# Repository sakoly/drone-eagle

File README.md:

# drone-eaglefile
ドローン制御用基板データ
dronesel5は電源用（フライトコントローラーとescに給電）
drone5はフライトコントローラー

基板作成支援アプリeagleで作成したドローンの基板データ
dps310(気圧センサ)：spi接続
minigps(みちびき対応GPS):uart接続
mpu9250(9軸センサ):spi接続
twelite(通信機):uart接続
HC-SR04(超音波センサ):degitalread(HIorLO)

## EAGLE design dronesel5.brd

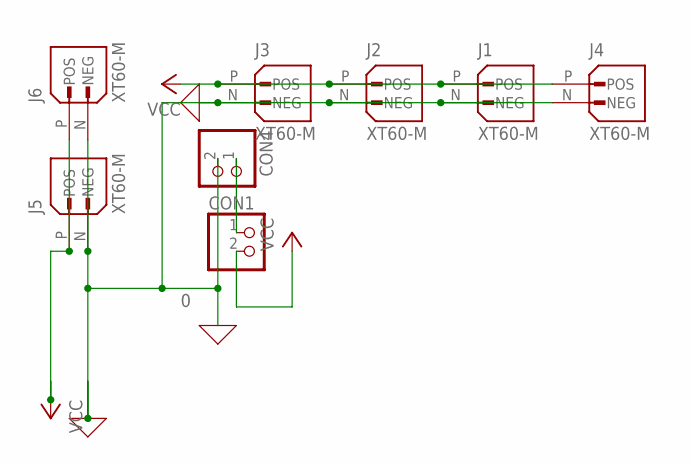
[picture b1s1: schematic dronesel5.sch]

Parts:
CON1, CON4: L2; L_2
J1, J2, J3, J4, J5, J6: XT60-M; AMASS_XT60-M

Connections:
0: CON4.2, J1.N (NEG), J2.N (NEG), J3.N (NEG), J4.N (NEG), J5.N (NEG), J6.N (NEG)
unnamed: CON1.1 (GND), CON4.1 (GND)
VCC: CON1.2, J1.P (POS), J2.P (POS), J3.P (POS), J4.P (POS), J5.P (POS), J6.P (POS)

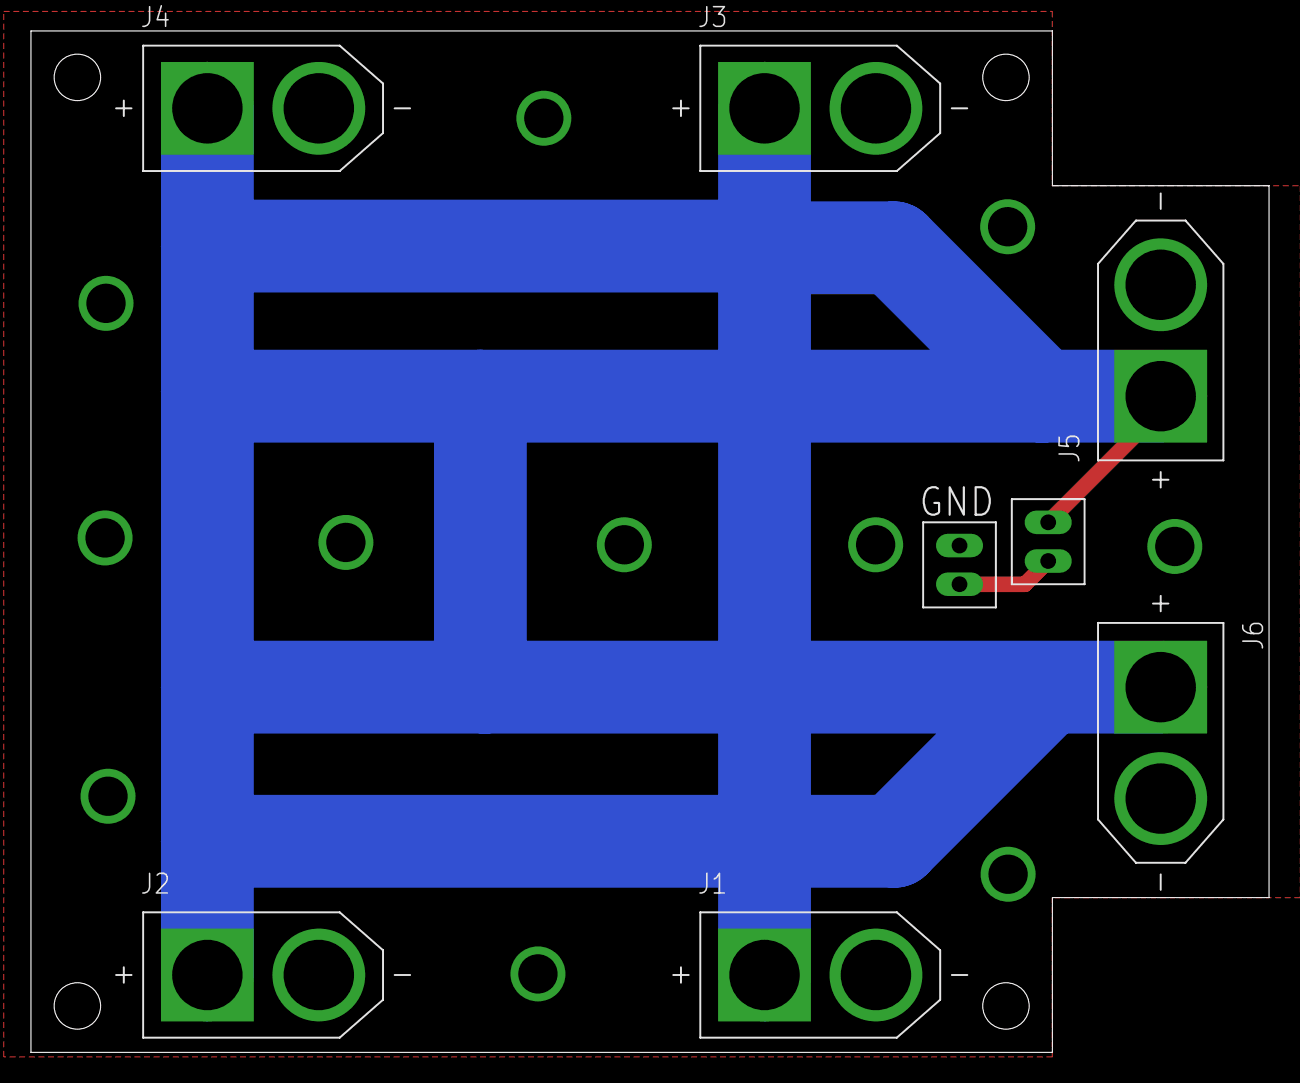
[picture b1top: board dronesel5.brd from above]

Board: 2 copper layers, 80.0 x 66.0 mm, 8 parts (0 on the bottom side), 3 nets.

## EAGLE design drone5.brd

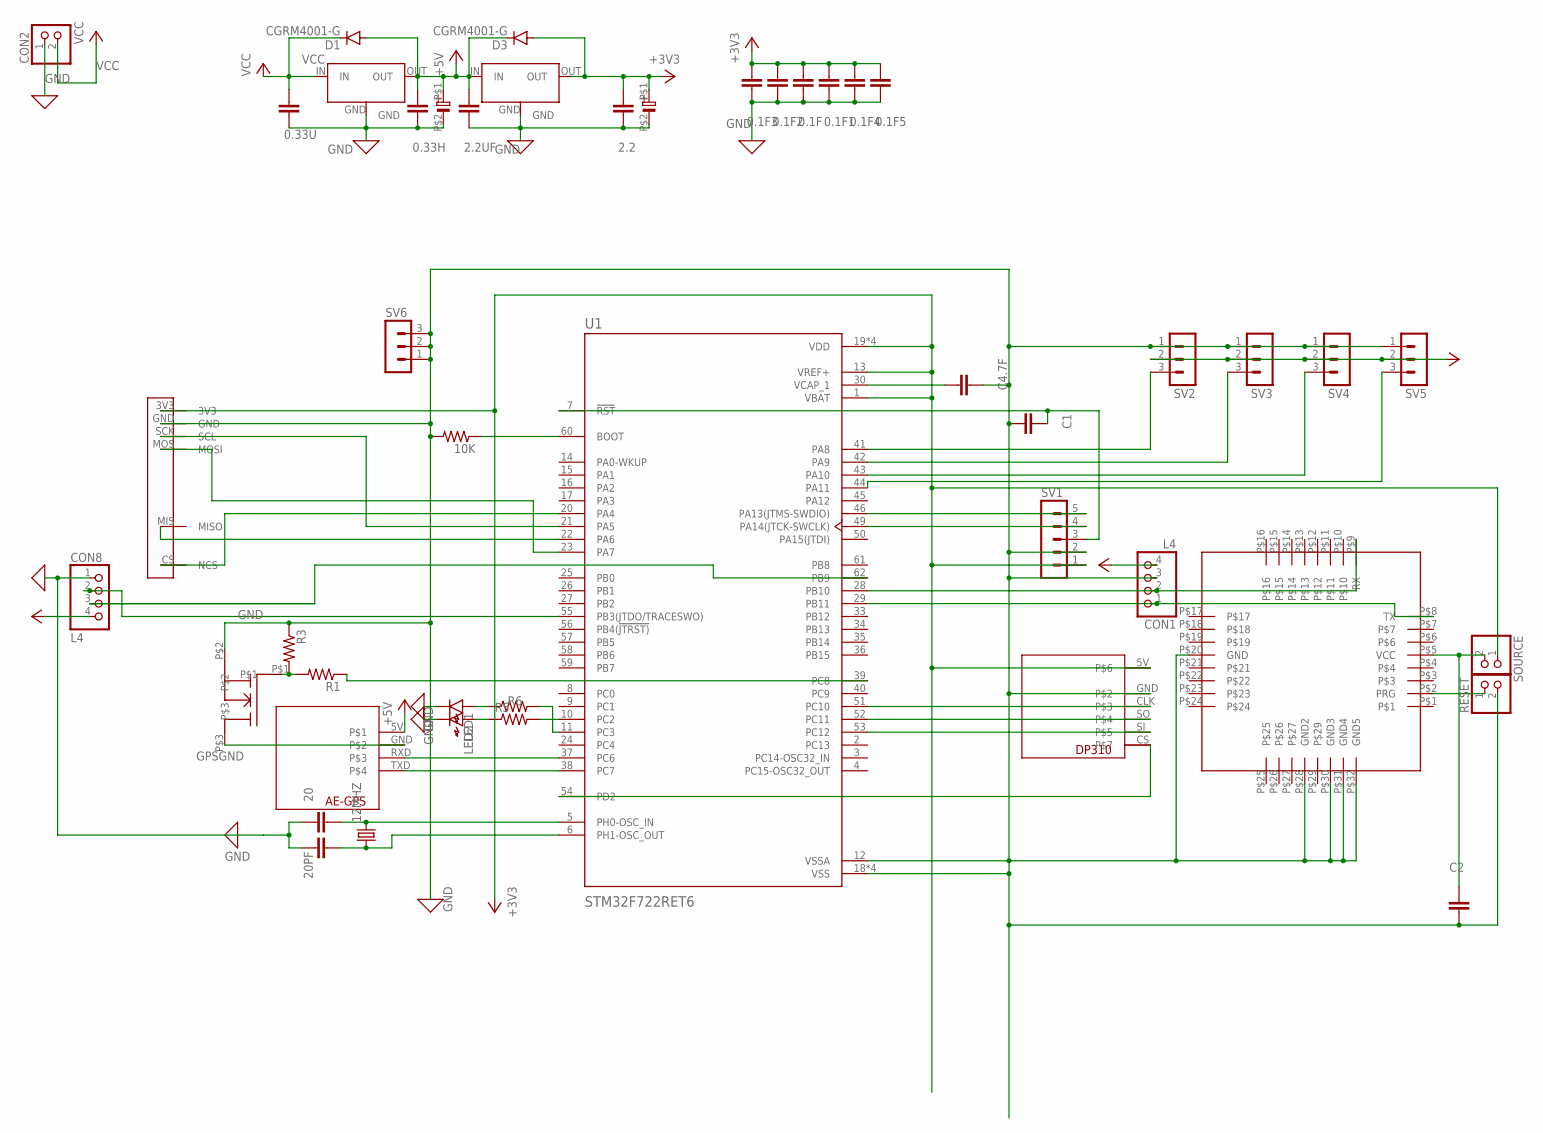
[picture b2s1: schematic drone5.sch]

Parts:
0.1F, 0.1F1, 0.1F2, 0.1F3, 0.1F4, 0.1F5, 0.33H, 0.33U, 2.2, 2.2UF, 20, 20PF: C-EUC0603; C0603
10K: R-US_R0603; R0603
12MHZ: CRYSTALHC49S; HC49/S
47, 47U: UCD0J470MCL1GS
C1, C2, C4.7F: C-EUC0603; C0603
CON1, CON8: L4; L_4
CON2: L2; L_2
CS1: DP310DP310; AE-GPS-HOLE
D1, D3: CGRM4001-G; SOD-123_MINI-SMA
LED1, LED2: LED1608
R1, R3, R5, R6: R-US_R0603; R0603
RESET: PINHD-1X2; 1X02
SOURCE: PINHD-1X2; 1X02
SV1: MA05-1
SV2, SV3, SV4, SV5, SV6: MA03-1
U1: STM32F722RET6; QFP50P1200X1200X160-64N
U$1: LITE
U$2: MPU9250
U$3: AE-GPS-HOLE
U$4, U$9: NJM2391DL1-33
U$7: SSM3K329R

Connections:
+3V3: 0.1F.1, 0.1F1.1, 0.1F2.1, 0.1F3.1, 0.1F4.1, 0.1F5.1, 2.2.1, 47.P$1 (+), CS1.5V, D3.A, SOURCE.1, SV1.1, U1.1 (VBAT), U1.13 (VREF+), U1.19 (VDD), U1.32 (VDD), U1.48 (VDD), U1.64 (VDD), U$2.3V3, U$4.OUT
+5V: 0.33H.1, 2.2UF.1, 47U.P$1 (+), CON1.4, CON8.4, D1.A, D3.C, SV2.2, SV3.2, SV4.2, SV5.2, U$3.5V, U$4.IN, U$9.OUT
CLK3: CS1.CLK, U1.51 (PC10)
GND: 0.1F.2, 0.1F1.2, 0.1F2.2, 0.1F3.2, 0.1F4.2, 0.1F5.2, 0.33H.2, 0.33U.2, 2.2.2, 2.2UF.2, 10K.2, 20.1, 20PF.1, 47.P$2 (ー), 47U.P$2 (ー), C1.1, C2.1, C4.7F.2, CON1.3, CON2.1 (GND), CON8.1, CS1.GND, LED1.K, LED2.K, R3.1, RESET.2, SV1.2, SV2.1, SV3.1, SV4.1, SV5.1, SV6.1, SV6.2, SV6.3, U1.12 (VSSA), U1.18 (VSS), U1.31 (VSS), U1.47 (VSS), U1.63 (VSS), U$1.P$20 (GND), U$1.P$28 (GND2), U$1.P$30 (GND3), U$1.P$31 (GND4), U$1.P$32 (GND5), U$2.GND, U$4.GND, U$7.P$2, U$9.GND
GPSGND: U$3.GND, U$7.P$3
MISO3: CS1.SO, U1.52 (PC11)
MOSI3: CS1.SI, U1.53 (PC12)
unnamed: 10K.1, U1.60 (BOOT)
unnamed: U1.21 (PA5), U$2.SCK (SCL)
unnamed: LED2.A, R5.1
unnamed: C4.7F.1, U1.30 (VCAP_1)
unnamed: SV1.5, U1.46 (PA13(JTMS-SWDIO))
unnamed: SV1.4, U1.49 (PA14(JTCK-SWCLK))
unnamed: CON1.1, U1.29 (PB11), U$1.P$8 (TX)
unnamed: CS1.CS, U1.54 (PD2)
unnamed: CON1.2, U1.28 (PB10), U$1.P$9 (RX)
unnamed: C2.2, SOURCE.2, U$1.P$5 (VCC)
unnamed: RESET.1, U$1.P$2 (PRG)
unnamed: U1.22 (PA6), U$2.MIS (MISO)
unnamed: SV2.3, U1.41 (PA8)
unnamed: SV3.3, U1.42 (PA9)
unnamed: SV4.3, U1.43 (PA10)
unnamed: SV5.3, U1.44 (PA11)
unnamed: R6.2, U1.11 (PC3)
unnamed: LED1.A, R6.1
unnamed: 12MHZ.1, 20PF.2, U1.6 (PH1-OSC_OUT)
unnamed: CON8.2, U1.55 (PB3(JTDO/TRACESWO))
unnamed: CON8.3, U1.62 (PB9)
unnamed: U1.23 (PA7), U$2.MOS (MOSI)
unnamed: U1.20 (PA4), U$2.CS (NCS)
unnamed: R5.2, U1.10 (PC2)
unnamed: R1.1, U1.39 (PC8)
unnamed: R1.2, R3.2, U$7.P$1
NRST: C1.2, SV1.3, U1.7 (!RST)
PH0_OSC_IN: 12MHZ.2, 20.2, U1.5 (PH0-OSC_IN)
UART6RX: U1.38 (PC7), U$3.TXD
UART6TX: U1.37 (PC6), U$3.RXD
VCC: 0.33U.1, CON2.2, D1.C, U$9.IN

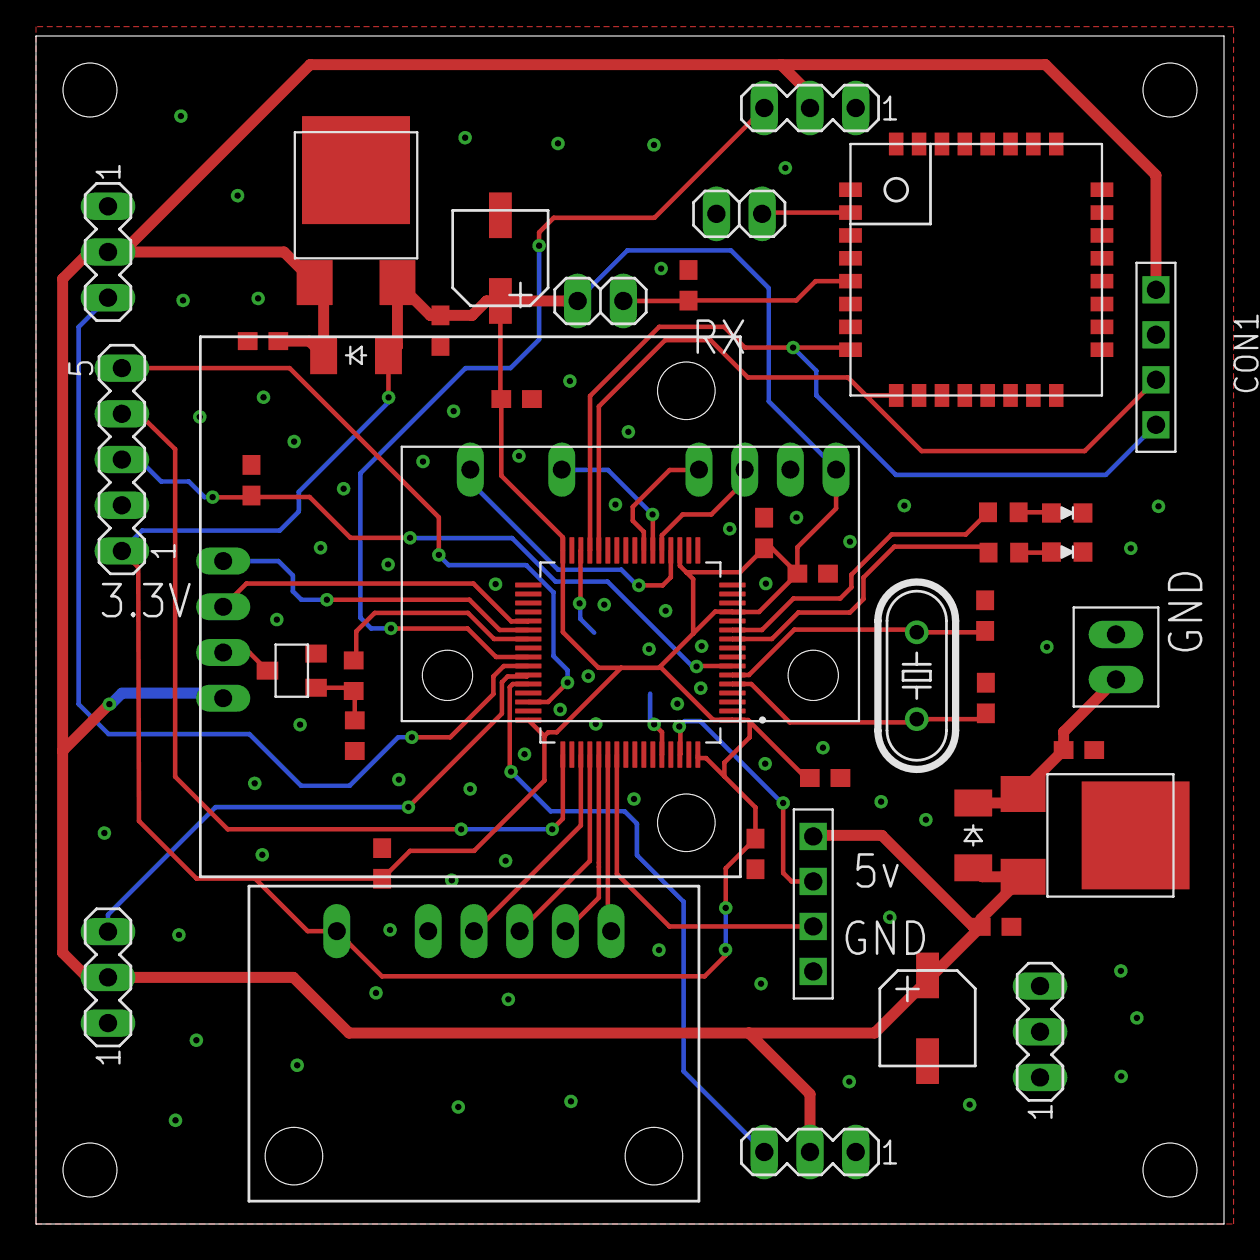
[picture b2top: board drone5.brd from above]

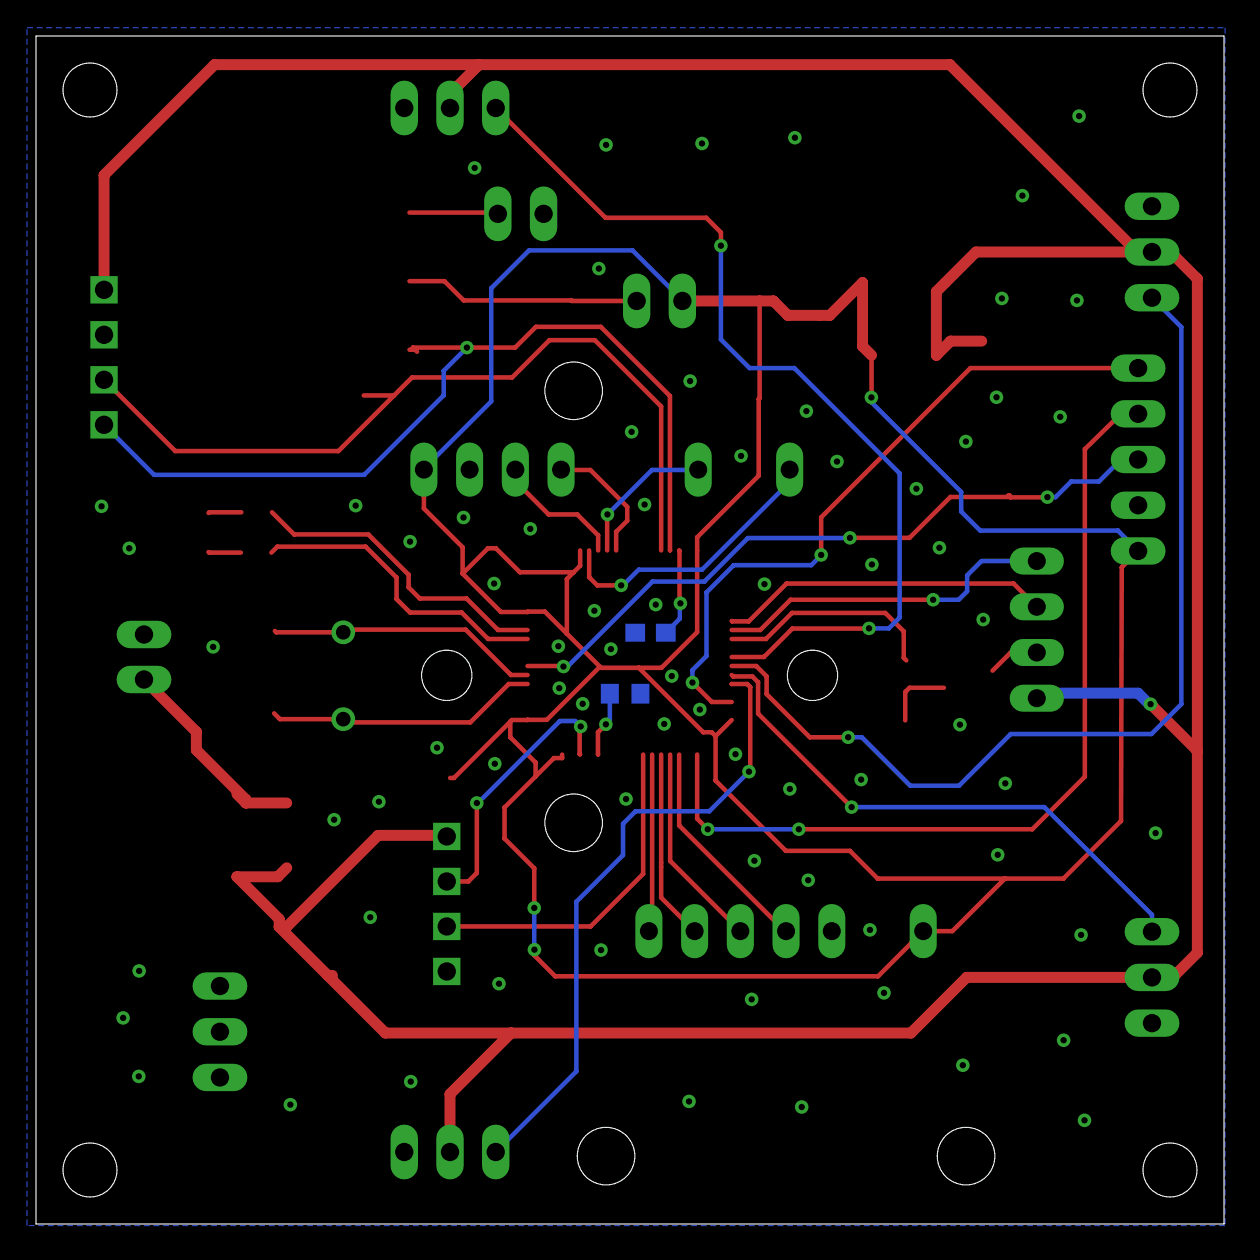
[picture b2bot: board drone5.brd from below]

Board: 2 copper layers, 66.0 x 66.0 mm, 46 parts (3 on the bottom side), 38 nets.

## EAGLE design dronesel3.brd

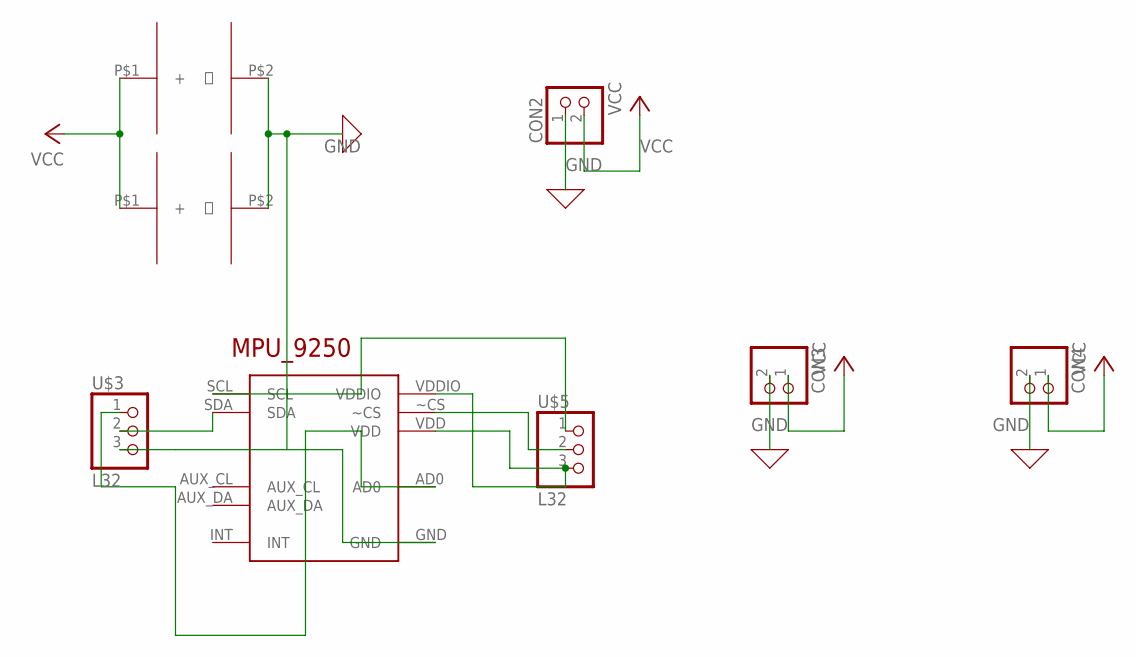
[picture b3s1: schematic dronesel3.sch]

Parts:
CON2, CON3, CON4: L2; L_2
MPU9250: MPU_9250
U$1, U$2: VEC5R4355QG-I
U$3, U$5: L32; L_32

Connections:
GND: CON2.1, CON3.2, CON4.2, MPU9250.GND, U$1.P$2 (ー), U$2.P$2 (ー), U$3.3
unnamed: MPU9250.VDD, MPU9250.VDDIO, U$5.3
unnamed: MPU9250.~CS, U$5.2
unnamed: MPU9250.SCL, U$5.1
unnamed: MPU9250.AD0, U$3.1
unnamed: MPU9250.SDA, U$3.2
VCC: CON2.2, CON3.1, CON4.1, U$1.P$1 (+), U$2.P$1 (+)

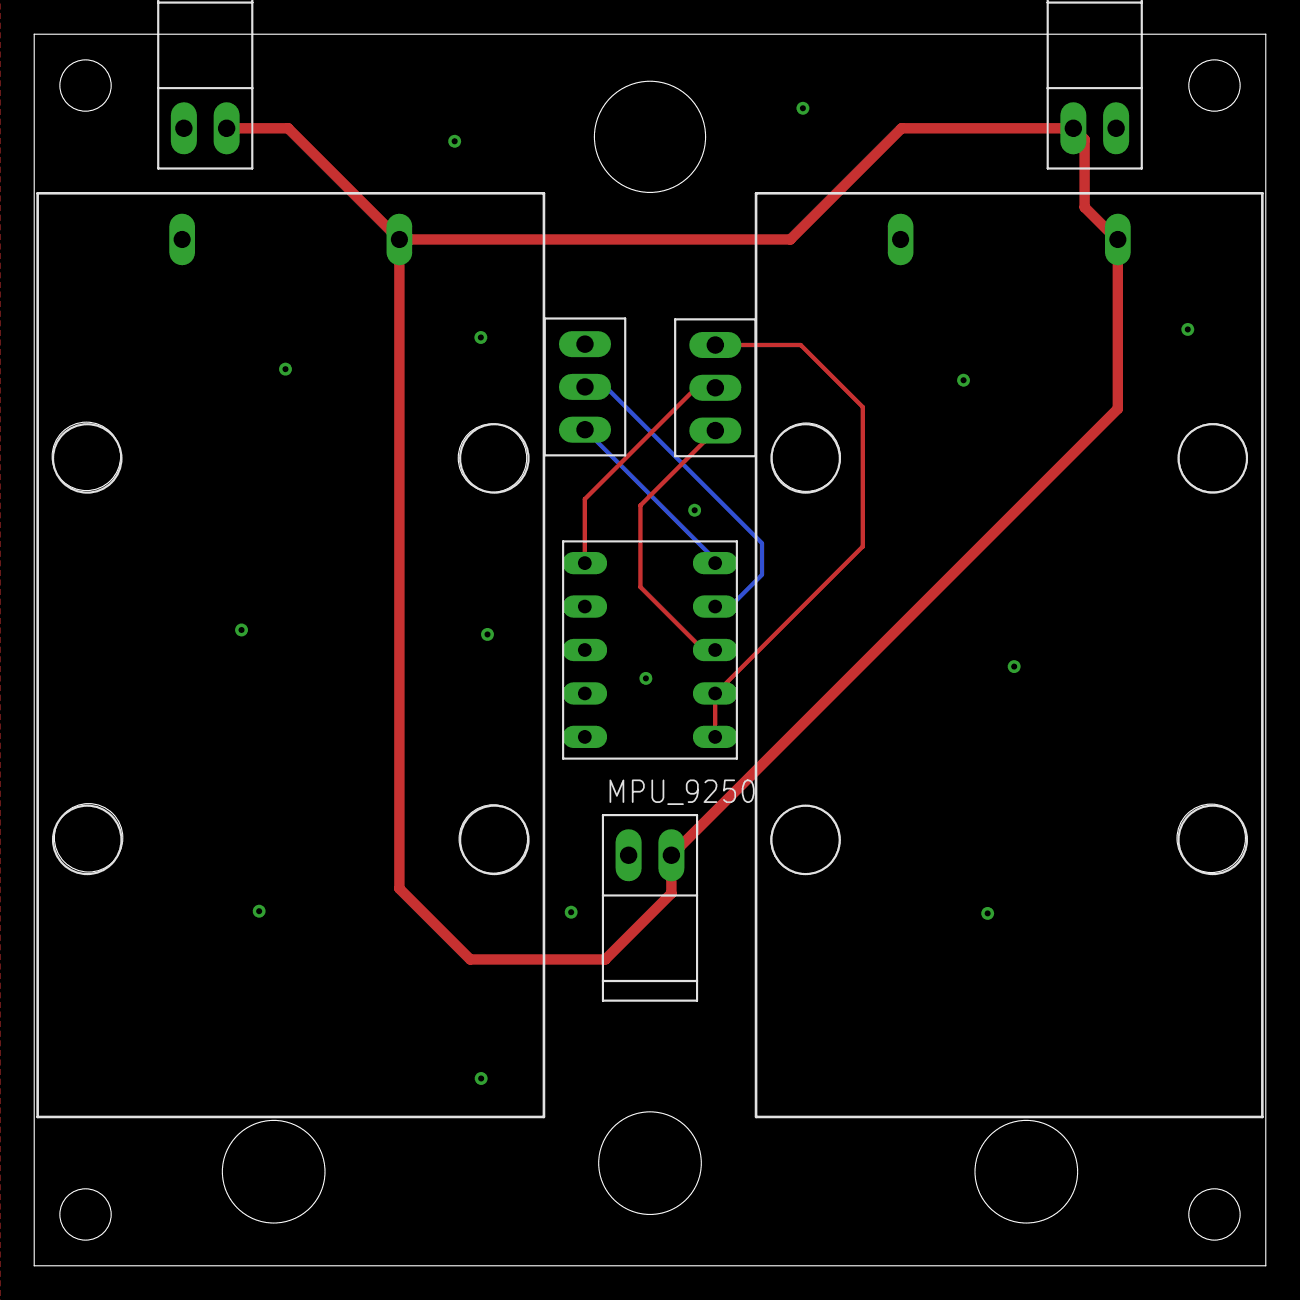
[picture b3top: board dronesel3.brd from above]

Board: 2 copper layers, 72.0 x 72.0 mm, 8 parts (0 on the bottom side), 7 nets.
